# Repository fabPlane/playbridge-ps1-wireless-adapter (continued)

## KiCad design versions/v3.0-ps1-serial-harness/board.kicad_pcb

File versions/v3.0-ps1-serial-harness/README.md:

# PlayBridge V3.0 — PS1 serial harness evaluation

Status: **J2 routing and combined firmware build pass; assembled V3 electrical
and simultaneous-load validation required before ordering**.

This directory is the authoritative V3.0 development project derived from the
validated, frozen V2.1 release. V3.0 repurposes the reserved J2 donor-harness
connector for a three-wire PS1 serial-port link while preserving the V2.1
status LEDs and connector-free UART0 service row.

## V3.0 design intent

- Evaluate whether the currently all-NC J2 can safely serve the PS1 serial
  harness before adding another connector. Do not populate both J2 and J4 for
  the same purpose without a documented mechanical/electrical reason.
- If J4 remains necessary, use one outward-facing USB-A connector body matching
  J1/J2 and identify it clearly as J4 and `NOT USB`.
- Preserve J1, J2, J3, the SERVICE / DEBUG row, RESET, BOOT, STATUS, PWR,
  antenna clearance, and all V2.1 functionality.
- Confirm the PS1 serial-harness pinout, logic levels, direction, protocol,
  throughput/latency, supported console revisions, and isolation/backfeed
  policy before committing copper. Do not silently parallel console buses.
- Keep the intended path explicit: PC/browser -> Wi-Fi -> ESP32 -> GPIO17/TX,
  GPIO16/RX and GND -> keyed NOT-USB harness -> PS1 serial port.
- The user/team confirmed the teammate firmware/protocol and electrical bench
  PoC on 2026-09-25. The preserved photos document the powered test hardware;
  functional operation is a user-reported bench result rather than something
  independently visible in the still images. Do not generalize that result to
  untested console revisions, cables, protocol modes, or full handshaking.

## V2.1 baseline retained

- D1 is the yellow-green firmware `STATUS` LED: KENTO `KT-0603YG` / LCSC `C2289`, driven by ESP32 module pin 26 on `STATUS_LED` through R13, 1 kΩ Yageo `RC0603FR-071KL` / `C22548`; polarity is unchanged.
- D6 is the red always-on 3V3 `PWR` LED: KENTO `KT-0603R` / `C2286`, through R29, 1 kΩ Yageo `RC0603FR-071KL` / `C22548`.
- The physical J4 header was removed. The lower-right SERVICE/DEBUG row contains DNP plated holes: TP2 GND at (43.500, 54.000) mm, TP3 UART_TX at (46.700, 54.000) mm, and TP4 UART_RX at (49.900, 54.000) mm. Pitch is 3.200 mm; each pad is 2.0 mm with a 1.0 mm finished plated hole.
- J1, J2, J3, and SERVICE / DEBUG are explicitly identified on F.Silkscreen. No J4 reference is fabricated in V2.1; V3.0 must first decide whether J2 can serve the serial harness or whether a distinct J4 is justified.
- TP1 remains the existing 3V3 test point. UART signals are 3.3 V logic only.
- RESET, BOOT, J1/J2/J3, USB orientations, antenna keepout, outline, and unrelated V2.0 placement/copper remain unchanged.

## Final verification and outputs

Verified 2026-09-25: DRC 0 errors, 0 unconnected, and only three approved historical `track_dangling` warnings; ERC 0 errors/0 warnings; schematic/PCB parity 0; release gate PASS.

- Accepted verification renders: `renders/service-debug-full-top.png` and `renders/service-debug-close.png`.
- Generic outputs: `exports/gerbers/`, `exports/gerbers/board.drl`, `exports/bom.csv`, `exports/positions.csv`, `exports/assembly-bom.csv`, `exports/assembly-cpl.csv`, `exports/netlist.net`, and `exports/fabrication.zip`.
- JLCPCB preparation: `ordering/jlcpcb-bom.csv`, `ordering/jlcpcb-cpl.csv`, and `ordering/gerbers-jlcpcb.zip`.
- Detailed evidence: `reports/V2.1-AUDIT.md`.
- V3.0 PoC evidence: `reports/evidence/README.md` and the two preserved setup
  photographs.
- V3.0 release result and package hashes: `reports/final-release-gate.md`.
- Combined firmware build evidence: `reports/V3.0-COMBINED-FIRMWARE.md`.

**ORDER HOLD:** fresh V3.0 manufacturing files include the fabricated J2
`NOT USB` warning. Before purchase, complete J2 voltage and signal-integrity
measurements, assembled-board simultaneous testing, and the BOM/CPL rotation,
substitution and live-stock review in `ordering/DO-NOT-ORDER.md`.

The fabrication exports and validation reports have been regenerated for V2.1.

V2 replaces the PCB-mounted PlayStation pin array with a removable donor-plug harness.

The main PlayBridge board will expose removable multi-contact connectors. A console-specific adapter will use a genuine donor controller cable and molded PlayStation male plug soldered to a matching breakout board. Swapping the adapter cable will make it possible to support other console systems without manufacturing their proprietary plug contacts directly on the main PCB.

## Architecture

- Keep the ESP32, signal protection and protocol-generation circuitry on the main board.
- Replace the console-facing PCB pin array with a removable cable interface.
- Use the genuine molded PlayStation donor plug for console alignment, contact geometry and insertion loads.
- Map every donor wire by continuity testing; never rely on wire color.
- Treat the observed missing pin 8 as a donor-plug property that must be verified electrically.
- Define connector pin allocation, power/backfeed protection, shield policy and cable requirements before designing the V2 PCB.
- Add other console adapters only after the PS1 harness is validated.

## Safety warning

The concept currently uses USB 3 Type-A connector hardware because it provides enough inexpensive contacts and readily available breakout boards. The signals would be native console signals—not USB. Any implementation must be clearly marked **NOT USB**, protected against accidental connection to computers/chargers, and reviewed before hardware is powered.

## References

- [`concepts/`](concepts/) contains the supplied system architecture, breakout-board example and illustrative product layout.
- [`references/ps1-donor-plug/`](references/ps1-donor-plug/) contains photographs of the actual donor plug, including the empty pin-8 position.

## V2.0.0 baseline checkpoint

This directory began as a self-contained copy of the V2.0.0 release snapshot. It includes the
KiCad project, FabDesk netlist/configuration, local symbol/footprint/3D-model
libraries, verification reports, manufacturing package, release tools,
references, and accepted renders.

The baseline details below remain useful for comparison, but V2.1 must pass a
fresh release gate after modification.

- Board: 56.295 × 62.000 mm, four layers, 1.20 mm thick.
- J1/J2: Hong Cheng `HC-USB3.0-L168-ZP` / JLCPCB `C7501856`, used as keyed nine-contact **non-USB** harness interfaces. J2 carries the validated three-wire PS1 serial link.
- The official JLCPCB/EasyEDA footprint and 3D model are stored locally. All nine electrical-pad centers exactly match the prior routed pattern; only the connector shell slots, body/courtyard and visual model changed.
- J1 is at (8.025, 50.825) mm and J2 at (26.025, 50.825) mm in the vendor footprint coordinate frame. Their absolute signal-pad coordinates and all routed copper are unchanged, and both mating mouths face outward through the lower edge. J3 remains at (51.025, 9.625) mm, 90°, facing outward through the right edge.
- ERC, DRC, schematic parity, and connectivity currently pass with zero errors, warnings, or unconnected items. Ordering remains subject to the sourcing and PCBA-completeness checks in `ordering/`.

See [`RELEASE-v2.0.0.md`](RELEASE-v2.0.0.md) for the release gate,
manufacturing-package status, 3D-model provenance, and remaining checkout hold.

## Snapshot layout

- `board.kicad_*`, `circuit.netlist.json`, and `fabdesk.json` — complete V2 design.
- `PlayBridge.pretty/`, `PlayBridge.3dshapes/`, and the symbol libraries — project-local libraries required to reopen the design.
- `ordering/` — Gerber archive, BOM, CPL, sourcing audit, and checkout hold.
- `reports/` — release build, DRC, ERC, statistics, and gate reports.
- `tools/` — scripts used for model inspection and order-file generation.
- `renders/` — accepted V2.0.0 renders only.

## USB-A mechanical fit

J1 and J2 use the official Hong Cheng `HC-USB3.0-L168-ZP` / `C7501856`
through-hole pattern: nine 0.70 mm signal holes plus two 0.60 × 2.30 mm plated
shell slots. The 13.10 × 16.80 mm body fits at the existing lower edge without
a PCB cutout; its mouth intentionally overhangs the board while all signal pins
and both shell slots remain supported by the PCB. Board thickness remains 1.20 mm.

## 3D-model validation

The official `C7501856` WRL/STEP model uses zero offset, zero rotation and unit
scale in the vendor footprint frame. Direct front and perspective renders show
both bodies seated on the top surface, the two mouths facing outward, and the
through-hole tails/retention legs aligned to their pads. See the accepted
`renders/v3.0-*.png` inspection set.

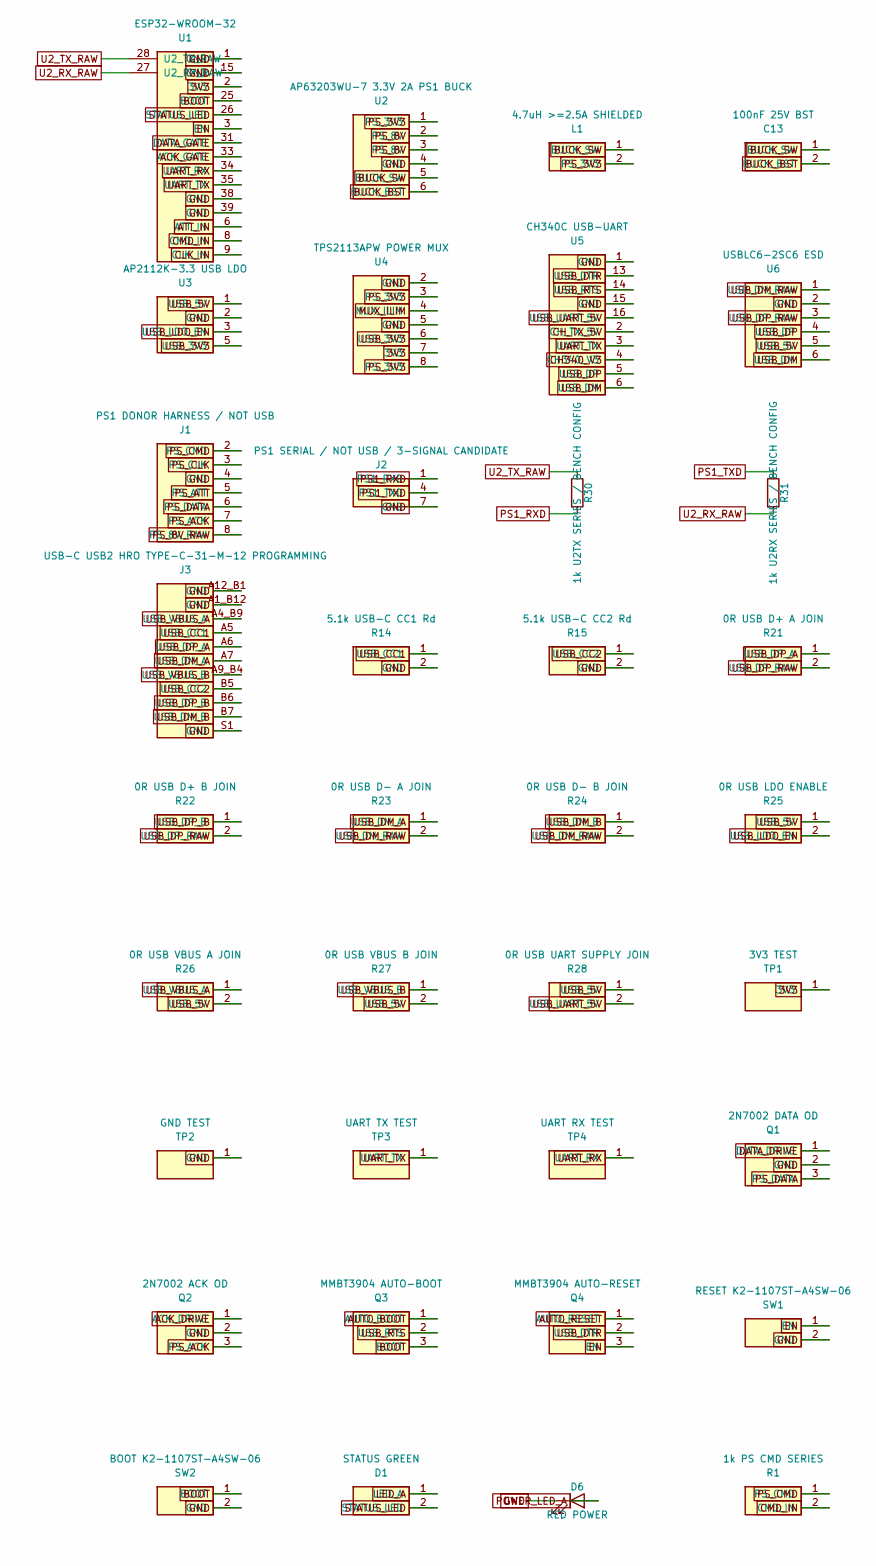
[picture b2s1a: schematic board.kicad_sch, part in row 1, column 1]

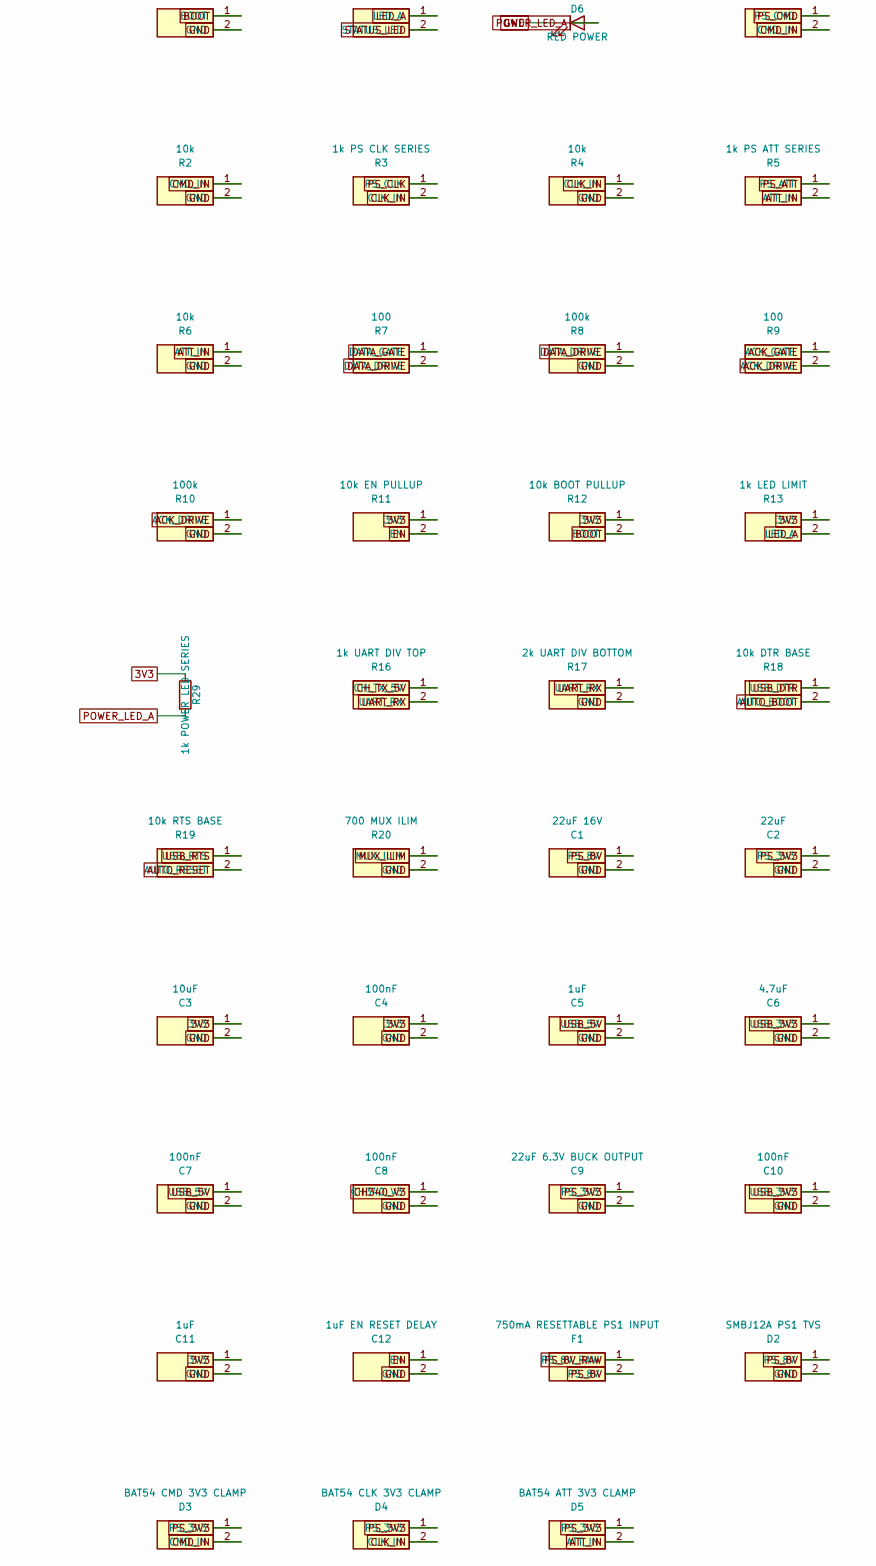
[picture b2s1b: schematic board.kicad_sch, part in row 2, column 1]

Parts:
C1: 22uF 16V; C_1206_3216Metric; MPN CL31A226KAHNNNE; JLCPCB/LCSC Part C12891
C2: 22uF; C_1206_3216Metric; MPN CL31A226KAHNNNE; JLCPCB/LCSC Part C12891
C3: 10uF; C_0805_2012Metric; MPN TCC0805X5R106K160FT; JLCPCB/LCSC Part C380332
C4, C7, C8, C10: 100nF; C_0603_1608Metric; MPN CC0603KRX7R9BB104; JLCPCB/LCSC Part C14663
C5, C11: 1uF; C_0603_1608Metric; MPN CL10A105KA8NNNC; JLCPCB/LCSC Part C5673
C6: 4.7uF; C_0805_2012Metric; MPN TCC0805X5R475K160FT; JLCPCB/LCSC Part C380342
C9: 22uF 6.3V BUCK OUTPUT; C_0805_2012Metric; MPN C0805X5R226M6R3NT; JLCPCB/LCSC Part C466795
C12: 1uF EN RESET DELAY; C_0603_1608Metric; MPN CL10A105KA8NNNC; JLCPCB/LCSC Part C5673
C13: 100nF 25V BST; C_0603_1608Metric; MPN CC0603KRX7R9BB104; JLCPCB/LCSC Part C14663
D1: STATUS GREEN; LED_0603_1608Metric; MPN 19-217/GHC-YR1S2/3T; JLCPCB/LCSC Part C72043
D2: SMBJ12A PS1 TVS; D_SMA; MPN SMAJ12A; JLCPCB/LCSC Part C908766
D3: BAT54 CMD 3V3 CLAMP; D_SOD-323_SILK_CLEAN; MPN BAT54WS; JLCPCB/LCSC Part C916997
D4: BAT54 CLK 3V3 CLAMP; D_SOD-323_SILK_CLEAN; MPN BAT54WS; JLCPCB/LCSC Part C916997
D5: BAT54 ATT 3V3 CLAMP; D_SOD-323_SILK_CLEAN; MPN BAT54WS; JLCPCB/LCSC Part C916997
D6: RED POWER; LED_0603_1608Metric; MPN KT-0603R; LCSC C2286
F1: 750mA RESETTABLE PS1 INPUT; Fuse_1206_3216Metric; MPN BSMD1206-075-30V; JLCPCB/LCSC Part C976305
J1: PS1 DONOR HARNESS / NOT USB; USB3_A_HongCheng_HC-USB3.0-L168-ZP_C7501856_PS1_FRONT_MODEL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; MPN HC-USB3.0-L168-ZP; JLCPCB/LCSC Part C7501856
J2: PS1 SERIAL / NOT USB / 3-SIGNAL CANDIDATE; USB3_A_HongCheng_HC-USB3.0-L168-ZP_C7501856_PS1_SERIAL_MODE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; MPN HC-USB3.0-L168-ZP; JLCPCB/LCSC Part C7501856
J3: USB-C USB2 HRO TYPE-C-31-M-12 PROGRAMMING; USB_C_Receptacle_HRO_TYPE-C-31-M-12_INTERIOR_FANOUT_V16_C16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; MPN TYPE-C-31-M-12; JLCPCB/LCSC Part C165948
L1: 4.7uH >=2.5A SHIELDED; L_Sunlord_SWPA4030S; MPN MCNR4030AF-4R7M; JLCPCB/LCSC Part C49449313
Q1: 2N7002 DATA OD; SOT-23_SILK_CLEAN_V2; MPN 2N7002; JLCPCB/LCSC Part C8545
Q2: 2N7002 ACK OD; SOT-23_SILK_CLEAN_V2; MPN 2N7002; JLCPCB/LCSC Part C8545
Q3: MMBT3904 AUTO-BOOT; SOT-23_SILK_CLEAN_V2; MPN MMBT3904(RANGE:100-300); JLCPCB/LCSC Part C20526
Q4: MMBT3904 AUTO-RESET; SOT-23_SILK_CLEAN_V2; MPN MMBT3904(RANGE:100-300); JLCPCB/LCSC Part C20526
R1: 1k PS CMD SERIES; R_0603_1608Metric_SILK_CLEAN; MPN 0603WAF1001T5E; JLCPCB/LCSC Part C21190
R2, R4, R6: 10k; R_0603_1608Metric_SILK_CLEAN; MPN 0603WAF1002T5E; JLCPCB/LCSC Part C25804
R3: 1k PS CLK SERIES; R_0603_1608Metric_SILK_CLEAN; MPN 0603WAF1001T5E; JLCPCB/LCSC Part C21190
R5: 1k PS ATT SERIES; R_0603_1608Metric_SILK_CLEAN; MPN 0603WAF1001T5E; JLCPCB/LCSC Part C21190
R7, R9: 100; R_0603_1608Metric_SILK_CLEAN; MPN 0603WAF1000T5E; JLCPCB/LCSC Part C22775
R8, R10: 100k; R_0603_1608Metric_SILK_CLEAN; MPN 0603WAF1003T5E; JLCPCB/LCSC Part C25803
R11: 10k EN PULLUP; R_0603_1608Metric_SILK_CLEAN; MPN 0603WAF1002T5E; JLCPCB/LCSC Part C25804
R12: 10k BOOT PULLUP; R_0603_1608Metric_SILK_CLEAN; MPN 0603WAF1002T5E; JLCPCB/LCSC Part C25804
R13: 1k LED LIMIT; R_0603_1608Metric_SILK_CLEAN; MPN 0603WAF1001T5E; JLCPCB/LCSC Part C21190
R14: 5.1k USB-C CC1 Rd; R_0402_1005Metric_SILK_CLEAN; MPN 0402WGF5101TCE; JLCPCB/LCSC Part C25905
R15: 5.1k USB-C CC2 Rd; R_0402_1005Metric_SILK_CLEAN; MPN 0402WGF5101TCE; JLCPCB/LCSC Part C25905
R16: 1k UART DIV TOP; R_0603_1608Metric_SILK_CLEAN; MPN 0603WAF1001T5E; JLCPCB/LCSC Part C21190
R17: 2k UART DIV BOTTOM; R_0603_1608Metric_SILK_CLEAN; MPN 0603WAF2001T5E; JLCPCB/LCSC Part C22975
R18: 10k DTR BASE; R_0603_1608Metric_SILK_CLEAN; MPN 0603WAF1002T5E; JLCPCB/LCSC Part C25804
R19: 10k RTS BASE; R_0603_1608Metric_SILK_CLEAN; MPN 0603WAF1002T5E; JLCPCB/LCSC Part C25804
R20: 700 MUX ILIM; R_0603_1608Metric_SILK_CLEAN; MPN RMS06FT6980; JLCPCB/LCSC Part C912219
R21: 0R USB D+ A JOIN; R_0402_1005Metric_SILK_CLEAN; MPN 0402WGF0000TCE; JLCPCB/LCSC Part C17168
R22: 0R USB D+ B JOIN; R_0402_1005Metric_SILK_CLEAN; MPN 0402WGF0000TCE; JLCPCB/LCSC Part C17168
R23: 0R USB D- A JOIN; R_0402_1005Metric_SILK_CLEAN; MPN 0402WGF0000TCE; JLCPCB/LCSC Part C17168
R24: 0R USB D- B JOIN; R_0402_1005Metric_SILK_CLEAN; MPN 0402WGF0000TCE; JLCPCB/LCSC Part C17168
R25: 0R USB LDO ENABLE; R_0402_1005Metric_SILK_CLEAN; MPN 0402WGF0000TCE; JLCPCB/LCSC Part C17168
R26: 0R USB VBUS A JOIN; R_0402_1005Metric_SILK_CLEAN; MPN 0402WGF0000TCE; JLCPCB/LCSC Part C17168
R27: 0R USB VBUS B JOIN; R_0402_1005Metric_SILK_CLEAN; MPN 0402WGF0000TCE; JLCPCB/LCSC Part C17168
R28: 0R USB UART SUPPLY JOIN; R_0402_1005Metric_SILK_CLEAN; MPN 0402WGF0000TCE; JLCPCB/LCSC Part C17168
R29: 1k POWER LED SERIES; R_0603_1608Metric; MPN 0603WAF1001T5E; LCSC C21190
R30: 1k U2TX SERIES / BENCH CONFIG; R_0603_1608Metric_SILK_CLEAN; MPN 0603WAF1001T5E; JLCPCB/LCSC Part C21190
R31: 1k U2RX SERIES / BENCH CONFIG; R_0603_1608Metric_SILK_CLEAN; MPN 0603WAF1001T5E; JLCPCB/LCSC Part C21190
SW1: RESET K2-1107ST-A4SW-06; SW_SPST_HRO_K2-1107ST-A4SW-06_RESET_V8; MPN K2-1107ST-A4SW-06; LCSC C2837195
SW2: BOOT K2-1107ST-A4SW-06; SW_SPST_HRO_K2-1107ST-A4SW-06_BOOT_V8; MPN K2-1107ST-A4SW-06; LCSC C2837195
TP1: 3V3 TEST; TestPoint_Pad_D1.5mm_SILK_CLEAN
TP2: GND TEST; TestPoint_THTPad_D2.0mm_Drill1.0mm
TP3: UART TX TEST; TestPoint_THTPad_D2.0mm_Drill1.0mm
TP4: UART RX TEST; TestPoint_THTPad_D2.0mm_Drill1.0mm
U1: ESP32-WROOM-32; ESP32-WROOM-32_D0.3mm_SILK_CLEAN; MPN ESP32-WROOM-32E-N4; JLCPCB/LCSC Part C701341
U2: AP63203WU-7 3.3V 2A PS1 BUCK; TSOT-23-6; MPN AP63203WU-7; JLCPCB/LCSC Part C780769
U3: AP2112K-3.3 USB LDO; SOT-23-5; MPN AP2112K-3.3TRG1; JLCPCB/LCSC Part C51118
U4: TPS2113APW POWER MUX; TSSOP-8_3x3mm_P0.65mm_AUTHORIZED_KICAD_COPY; MPN TPS2113APWR; JLCPCB/LCSC Part C130052
U5: CH340C USB-UART; SOIC-16_3.9x9.9mm_P1.27mm_SILK_CLEAN; MPN CH340C; JLCPCB/LCSC Part C7464026
U6: USBLC6-2SC6 ESD; SOT-23-6; MPN USBLC6-2SC6; JLCPCB/LCSC Part C7519

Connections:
3V3: C3.1 (3V3), C4.1 (3V3), C11.1 (3V3), R11.1 (3V3), R12.1 (3V3), R13.1 (3V3), R29.1, TP1.1 (3V3_1), U1.2 (3V3), U4.7 (3V3)
ACK_DRIVE: Q2.1 (ACK_DRIVE), R9.2 (ACK_DRIVE), R10.1 (ACK_DRIVE)
ACK_GATE: R9.1 (ACK_GATE), U1.33 (ACK_GATE)
ATT_IN: D5.2 (ATT_IN), R5.2 (ATT_IN), R6.1 (ATT_IN), U1.6 (ATT_IN)
AUTO_BOOT: Q3.1 (AUTO_BOOT), R18.2 (AUTO_BOOT)
AUTO_RESET: Q4.1 (AUTO_RESET), R19.2 (AUTO_RESET)
BOOT: Q3.3 (BOOT), R12.2 (BOOT), SW2.1 (BOOT), U1.25 (BOOT)
BUCK_BST: C13.2 (BUCK_BST), U2.6 (BUCK_BST)
BUCK_SW: C13.1 (BUCK_SW), L1.1 (BUCK_SW), U2.5 (BUCK_SW)
CH340_V3: C8.1 (CH340_V3), U5.4 (CH340_V3)
CH_TX_5V: R16.1 (CH_TX_5V), U5.2 (CH_TX_5V)
CLK_IN: D4.2 (CLK_IN), R3.2 (CLK_IN), R4.1 (CLK_IN), U1.9 (CLK_IN)
CMD_IN: D3.2 (CMD_IN), R1.2 (CMD_IN), R2.1 (CMD_IN), U1.8 (CMD_IN)
DATA_DRIVE: Q1.1 (DATA_DRIVE), R7.2 (DATA_DRIVE), R8.1 (DATA_DRIVE)
DATA_GATE: R7.1 (DATA_GATE), U1.31 (DATA_GATE)
EN: C12.1 (EN), Q4.3 (EN), R11.2 (EN), SW1.1 (EN), U1.3 (EN)
GND: C1.2 (GND), C2.2 (GND), C3.2 (GND), C4.2 (GND), C5.2 (GND), C6.2 (GND), C7.2 (GND), C8.2 (GND), C9.2 (GND), C10.2 (GND), C11.2 (GND), C12.2 (GND), D2.2 (GND), D6.1 (K), J1.4 (GND), J2.7 (GND), J3.A1_B12 (GND), J3.A12_B1 (GND), J3.S1 (GND), Q1.2 (GND), Q2.2 (GND), R2.2 (GND), R4.2 (GND), R6.2 (GND), R8.2 (GND), R10.2 (GND), R14.2 (GND), R15.2 (GND), R17.2 (GND), R20.2 (GND), SW1.2 (GND), SW2.2 (GND), TP2.1 (GND_1), U1.1 (GND), U1.15 (GND), U1.38 (GND), U1.39 (GND), U2.4 (GND), U3.2 (GND), U4.2 (GND), U4.5 (GND), U5.1 (GND), U5.15 (GND), U6.2 (GND)
LED_A: D1.1 (LED_A), R13.2 (LED_A)
MUX_ILIM: R20.1 (MUX_ILIM), U4.4 (MUX_ILIM)
POWER_LED_A: D6.2 (A), R29.2
PS1_RXD: J2.1 (PS1_RXD), R30.2
PS1_TXD: J2.4 (PS1_TXD), R31.1
PS_3V3: C2.1 (PS_3V3), C9.1 (PS_3V3), D3.1 (PS_3V3), D4.1 (PS_3V3), D5.1 (PS_3V3), L1.2 (PS_3V3), U2.1 (PS_3V3), U4.3 (PS_3V3), U4.8 (PS_3V3)
PS_8V: C1.1 (PS_8V), D2.1 (PS_8V), F1.2 (PS_8V), U2.2 (PS_8V), U2.3 (PS_8V)
PS_8V_RAW: F1.1 (PS_8V_RAW), J1.8 (PS_8V_RAW)
PS_ACK: J1.7 (PS_ACK), Q2.3 (PS_ACK)
PS_ATT: J1.5 (PS_ATT), R5.1 (PS_ATT)
PS_CLK: J1.3 (PS_CLK), R3.1 (PS_CLK)
PS_CMD: J1.2 (PS_CMD), R1.1 (PS_CMD)
PS_DATA: J1.6 (PS_DATA), Q1.3 (PS_DATA)
STATUS_LED: D1.2 (STATUS_LED), U1.26 (STATUS_LED)
U2_RX_RAW: R31.2, U1.27 (U2_RX_RAW)
U2_TX_RAW: R30.1, U1.28 (U2_TX_RAW)
UART_RX: R16.2 (UART_RX), R17.1 (UART_RX), TP4.1 (UART_RX_1), U1.34 (UART_RX)
UART_TX: TP3.1 (UART_TX_1), U1.35 (UART_TX), U5.3 (UART_TX)
USB_3V3: C6.1 (USB_3V3), C10.1 (USB_3V3), U3.5 (USB_3V3), U4.6 (USB_3V3)
USB_5V: C5.1 (USB_5V), C7.1 (USB_5V), R25.1 (USB_5V), R26.2 (USB_5V), R27.2 (USB_5V), R28.1 (USB_5V), U3.1 (USB_5V), U6.5 (USB_5V)
USB_CC1: J3.A5 (USB_CC1), R14.1 (USB_CC1)
USB_CC2: J3.B5 (USB_CC2), R15.1 (USB_CC2)
USB_DM: U5.6 (USB_DM), U6.6 (USB_DM)
USB_DM_A: J3.A7 (USB_DM_A), R23.1 (USB_DM_A)
USB_DM_B: J3.B7 (USB_DM_B), R24.1 (USB_DM_B)
USB_DM_RAW: R23.2 (USB_DM_RAW), R24.2 (USB_DM_RAW), U6.1 (USB_DM_RAW)
USB_DP: U5.5 (USB_DP), U6.4 (USB_DP)
USB_DP_A: J3.A6 (USB_DP_A), R21.1 (USB_DP_A)
USB_DP_B: J3.B6 (USB_DP_B), R22.1 (USB_DP_B)
USB_DP_RAW: R21.2 (USB_DP_RAW), R22.2 (USB_DP_RAW), U6.3 (USB_DP_RAW)
USB_DTR: Q4.2 (USB_DTR), R18.1 (USB_DTR), U5.13 (USB_DTR)
USB_LDO_EN: R25.2 (USB_LDO_EN), U3.3 (USB_LDO_EN)
USB_RTS: Q3.2 (USB_RTS), R19.1 (USB_RTS), U5.14 (USB_RTS)
USB_UART_5V: R28.2 (USB_UART_5V), U5.16 (USB_UART_5V)
USB_VBUS_A: J3.A4_B9 (USB_VBUS_A), R26.1 (USB_VBUS_A)
USB_VBUS_B: J3.A9_B4 (USB_VBUS_B), R27.1 (USB_VBUS_B)

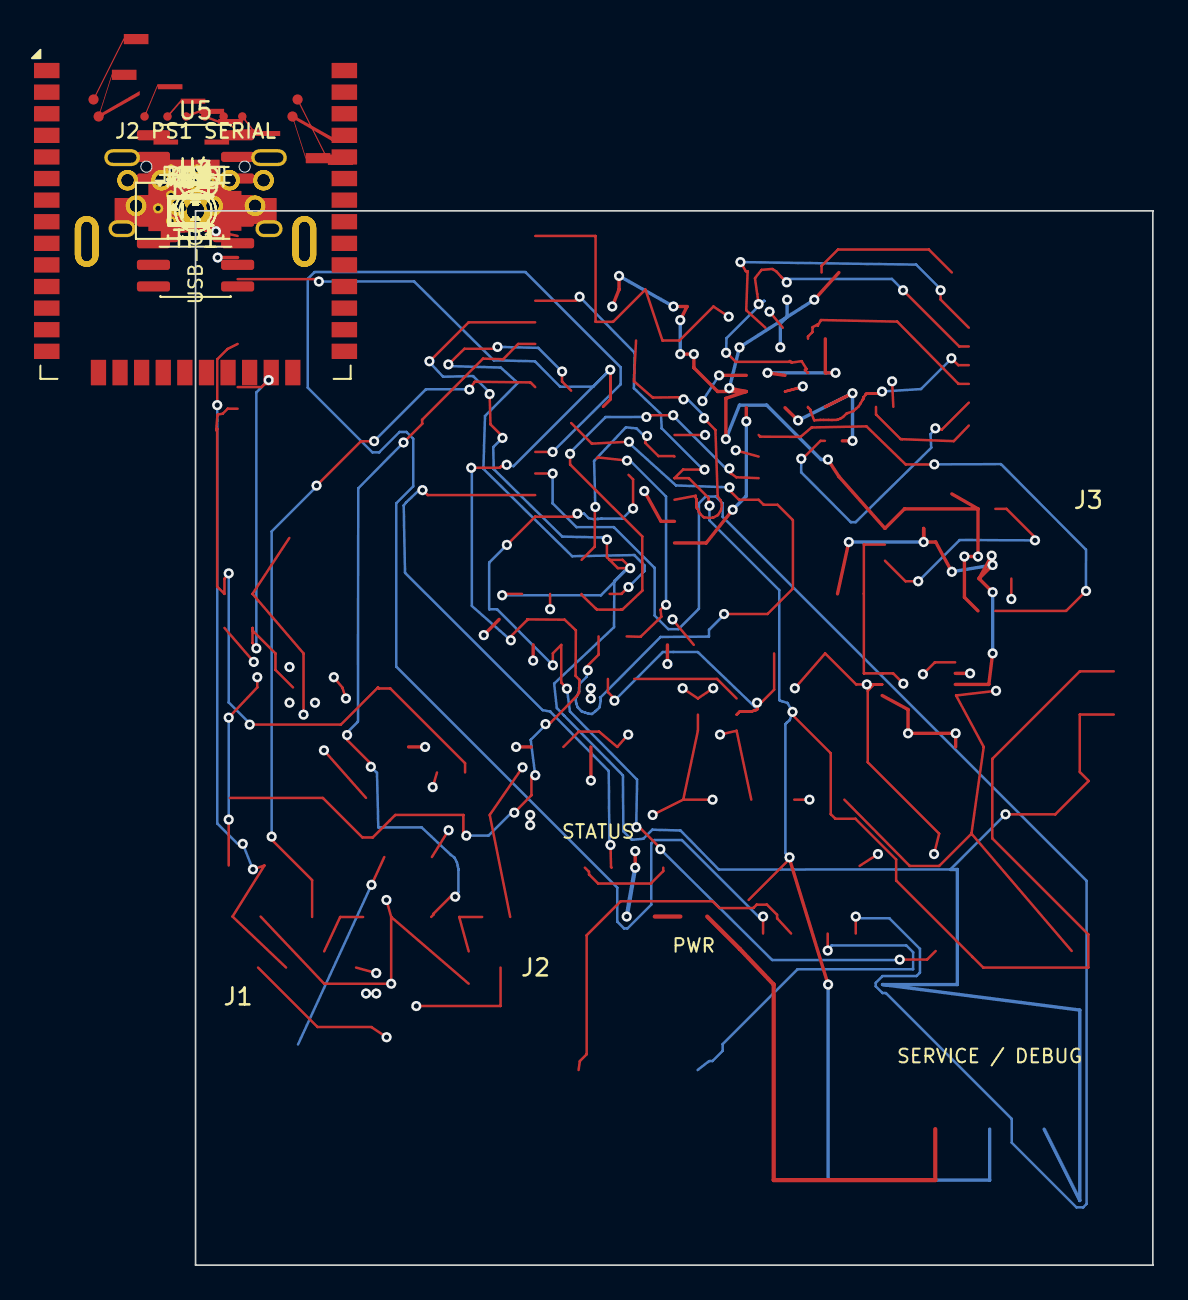
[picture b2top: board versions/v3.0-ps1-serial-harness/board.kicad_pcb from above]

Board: 4 copper layers, 56.3 x 62.0 mm, 71 parts (0 on the bottom side), 53 nets.

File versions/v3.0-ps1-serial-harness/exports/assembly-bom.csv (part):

"Reference","Value","Footprint","Assembly","DNP","Datasheet","Engineering Note","Footprint Provenance","Function","Hole","JLCPCB Part URL","JLCPCB/LCSC Part","LCSC","Label","MPN","Manufacturer","Normalized Manufacturer Number","Orientation","Package","Pad","Pinout","Placement Constraint","Procurement Status","Safety"
"C1","22uF 16V","PlayBridge:C_1206_3216Metric","","","","","","","","https://jlcpcb.com/partdetail/C12891","C12891","C12891","","CL31A226KAHNNNE","Samsung Electro-Mechanics","","","1206, 22uF, 25V, X5R, +/-10%","","","","JLCPCB sourcing selection verified 2026-09-25",""
"C2","22uF","PlayBridge:C_1206_3216Metric","","","","","","","","https://jlcpcb.com/partdetail/C12891","C12891","C12891","","CL31A226KAHNNNE","Samsung Electro-Mechanics","","","1206, 22uF, 25V, X5R, +/-10%","","","","JLCPCB sourcing selection verified 2026-09-25",""
"C3","10uF","PlayBridge:C_0805_2012Metric","","","","","","","","https://jlcpcb.com/partdetail/C1713","C1713","C1713","","CL21A106KOQNNNE","Samsung Electro-Mechanics","","","0805, 10uF, 16V, X5R, +/-10%","","","","JLCPCB sourcing selection verified 2026-09-25",""
"C4","100nF","PlayBridge:C_0603_1608Metric","","","","","","","","https://jlcpcb.com/partdetail/C14663","C14663","C14663","","CC0603KRX7R9BB104","Yageo","","","0603, 100nF, 50V, X7R, +/-10%","","","","JLCPCB sourcing selection verified 2026-09-25",""
"C5","1uF","PlayBridge:C_0603_1608Metric","","","","","","","","https://jlcpcb.com/partdetail/C5673","C5673","C5673","","CL10A105KA8NNNC","Samsung Electro-Mechanics","","","0603, 1uF, 25V, X5R, +/-10%","","","","JLCPCB sourcing selection verified 2026-09-25",""
"C6","4.7uF","PlayBridge:C_0805_2012Metric","","","","","","","","https://jlcpcb.com/partdetail/C380342","C380342","C380342","","TCC0805X5R475K160FT","CCTC","","","0805, 4.7uF, 16V, X5R, +/-10%","","","","JLCPCB sourcing selection verified 2026-09-25",""
"C7","100nF","PlayBridge:C_0603_1608Metric","","","","","","","","https://jlcpcb.com/partdetail/C14663","C14663","C14663","","CC0603KRX7R9BB104","Yageo","","","0603, 100nF, 50V, X7R, +/-10%","","","","JLCPCB sourcing selection verified 2026-09-25",""
"C8","100nF","PlayBridge:C_0603_1608Metric","","","","","","","","https://jlcpcb.com/partdetail/C14663","C14663","C14663","","CC0603KRX7R9BB104","Yageo","","","0603, 100nF, 50V, X7R, +/-10%","","","","JLCPCB sourcing selection verified 2026-09-25",""
"C9","22uF 6.3V BUCK OUTPUT","PlayBridge:C_0805_2012Metric","","","","","","","","https://jlcpcb.com/partdetail/C5674","C5674","C5674","","CL21A226MQQNNNE","Samsung Electro-Mechanics","","","0805, 22uF, 6.3V, X5R, +/-20%","","","","JLCPCB sourcing selection verified 2026-09-25",""
"C10","100nF","PlayBridge:C_0603_1608Metric","","","","","","","","https://jlcpcb.com/partdetail/C14663","C14663","C14663","","CC0603KRX7R9BB104","Yageo","","","0603, 100nF, 50V, X7R, +/-10%","","","","JLCPCB sourcing selection verified 2026-09-25",""
"C11","1uF","PlayBridge:C_0603_1608Metric","","","","","","","","https://jlcpcb.com/partdetail/C5673","C5673","C5673","","CL10A105KA8NNNC","Samsung Electro-Mechanics","","","0603, 1uF, 25V, X5R, +/-10%","","","","JLCPCB sourcing selection verified 2026-09-25",""
"C12","1uF EN RESET DELAY","PlayBridge:C_0603_1608Metric","","","","","","","","https://jlcpcb.com/partdetail/C5673","C5673","C5673","","CL10A105KA8NNNC","Samsung Electro-Mechanics","","","0603, 1uF, 25V, X5R, +/-10%","","","","JLCPCB sourcing selection verified 2026-09-25",""
"C13","100nF 25V BST","PlayBridge:C_0603_1608Metric","","","","","","","","https://jlcpcb.com/partdetail/C14663","C14663","C14663","","CC0603KRX7R9BB104","Yageo","","","0603, 100nF, 50V, X7R, +/-10%","","","","JLCPCB sourcing selection verified 2026-09-25",""
"D1","STATUS YELLOW-GREEN","PlayBridge:LED_0603_1608Metric","","","","","","","","https://jlcpcb.com/partdetail/C2289","C2289","C2289","","KT-0603YG","KENTO","","","0603 yellow-green LED","","","","JLCPCB sourcing selection verified 2026-09-25",""
"D2","SMBJ12A PS1 TVS","PlayBridge:D_SMA","","","","Corrected from SMBJ12A: PCB footprint is DO-214AC/SMA. Electrical rating remains 12V standoff, unidirectional TVS.","","","","https://jlcpcb.com/partdetail/C908766","C908766","C908766","","SMAJ12A","GOODWORK","","","DO-214AC (SMA), 12V standoff, 400W unidirectional TVS","","","","JLCPCB sourcing selection verified 2026-09-25",""
"D3","BAT54 CMD 3V3 CLAMP","PlayBridge:D_SOD-323_SILK_CLEAN","","","","","","","","https://jlcpcb.com/partdetail/C916997","C916997","C916997","","BAT54WS","JSMSEMI","","","SOD-323 Schottky diode","","","","JLCPCB sourcing selection verified 2026-09-25",""
"D4","BAT54 CLK 3V3 CLAMP","PlayBridge:D_SOD-323_SILK_CLEAN","","","","","","","","https://jlcpcb.com/partdetail/C916997","C916997","C916997","","BAT54WS","JSMSEMI","","","SOD-323 Schottky diode","","","","JLCPCB sourcing selection verified 2026-09-25",""
"D5","BAT54 ATT 3V3 CLAMP","PlayBridge:D_SOD-323_SILK_CLEAN","","","","","","","","https://jlcpcb.com/partdetail/C916997","C916997","C916997","","BAT54WS","JSMSEMI","","","SOD-323 Schottky diode","","","","JLCPCB sourcing selection verified 2026-09-25",""
"D6","RED POWER","LED_SMD:LED_0603_1608Metric","","","","","","Always-on 3V3 POWER indicator","","","C2286","C2286","","KT-0603R","KENTO","","","0603 red LED","","","","",""
"F1","750mA RESETTABLE PS1 INPUT","PlayBridge:Fuse_1206_3216Metric","","","","","","","","https://jlcpcb.com/partdetail/C976305","C976305","C976305","","BSMD1206-075-30V","BHFUSE","","","1206 resettable fuse, 750mA hold, 1.5A trip, 30V","","","","JLCPCB sourcing selection verified 2026-09-25",""
"J1","PS1 DONOR HARNESS / NOT USB","PlayBridge:USB3_A_HongCheng_HC-USB3.0-L168-ZP_C7501856_PS1_FRONT_MODEL_V3","","","https://jlcpcb.com/partdetail/HongCheng-HC_USB3_0_L168ZP/C7501856","","Official JLCPCB/EasyEDA C7501856 land geometry for Hong Cheng HC-USB3.0-L168-ZP, converted locally with easyeda2kicad.","","","https://jlcpcb.com/partdetail/HongCheng-HC_USB3_0_L168ZP/C7501856","C7501856","C7501856","","HC-USB3.0-L168-ZP","Hong Cheng","HC-USB3.0-L168-ZP","Right-angle top-mount receptacle at the lower board edge; mating mouth faces outward. Signal-pad coordinates are preserved from the validated board routing.","USB 3.0 Type-A right-angle through-hole receptacle, 9 signal pins + 2 shell slots","","CUSTOM NON-USB. Standard USB contact identities: 1/VBUS=NC_KEY; 2/D-=PS_CMD; 3/D+=PS_CLK; 4/GND=GND; 5/SSRX-=PS_ATT; 6/SSRX+=PS_DATA; 7/GND_DRAIN=PS_ACK; 8/SSTX-=PS_8V_RAW; 9/SSTX+=PS_3V5_CONSOLE_ISOLATED_NC. Shell pads SH have no electrical net.","","JLCPCB in-stock assembly part verified 2026-09-25; recheck live stock at order time","NOT USB. Pad 1 is deliberately unconnected so a normal USB source VBUS does not enter the circuit. Pad 9 is physically present but has no PCB net or copper and must never be tied to board 3V3. Shell is mechanically anchored but electrically isolated. NOT PRODUCTION RELEASED."
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
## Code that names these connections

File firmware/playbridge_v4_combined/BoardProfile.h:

#pragma once
#include <stdint.h>

// Select explicitly: 1 = console-tested Node32 breadboard, 2 = V4 PCB map.
// Profile 2 is compile-checked, not physical-PCBA qualified.
#ifndef PLAYBRIDGE_PROFILE
#define PLAYBRIDGE_PROFILE 1
#endif
#if PLAYBRIDGE_PROFILE == 1
static constexpr uint8_t CMD = 34, CLK = 32, ATT = 21;
static constexpr uint8_t DATA_DRIVE = 33, ACK_DRIVE = 27, DATA_SENSE = 19;
static constexpr bool HAS_DATA_READBACK = true;
static constexpr const char *PROFILE_NAME = "bench-cmd34-data19";
#elif PLAYBRIDGE_PROFILE == 2
static constexpr uint8_t CMD = 19, CLK = 32, ATT = 21;
static constexpr uint8_t DATA_DRIVE = 33, ACK_DRIVE = 27;
// Placeholder never configured/read; GPIO34 on PCB is ACK sense, NOT DATA.
static constexpr uint8_t DATA_SENSE = 34;
static constexpr bool HAS_DATA_READBACK = false;
static constexpr const char *PROFILE_NAME = "v4-pcb-unqualified";
#else
#error Select PLAYBRIDGE_PROFILE=1 (bench) or 2 (V4 PCB)
#endif
static constexpr int UART_RX = 16, UART_TX = 17;
static_assert(CMD != UART_RX && CMD != UART_TX && DATA_DRIVE != UART_TX,
              "Controller and serial pins must not overlap");
